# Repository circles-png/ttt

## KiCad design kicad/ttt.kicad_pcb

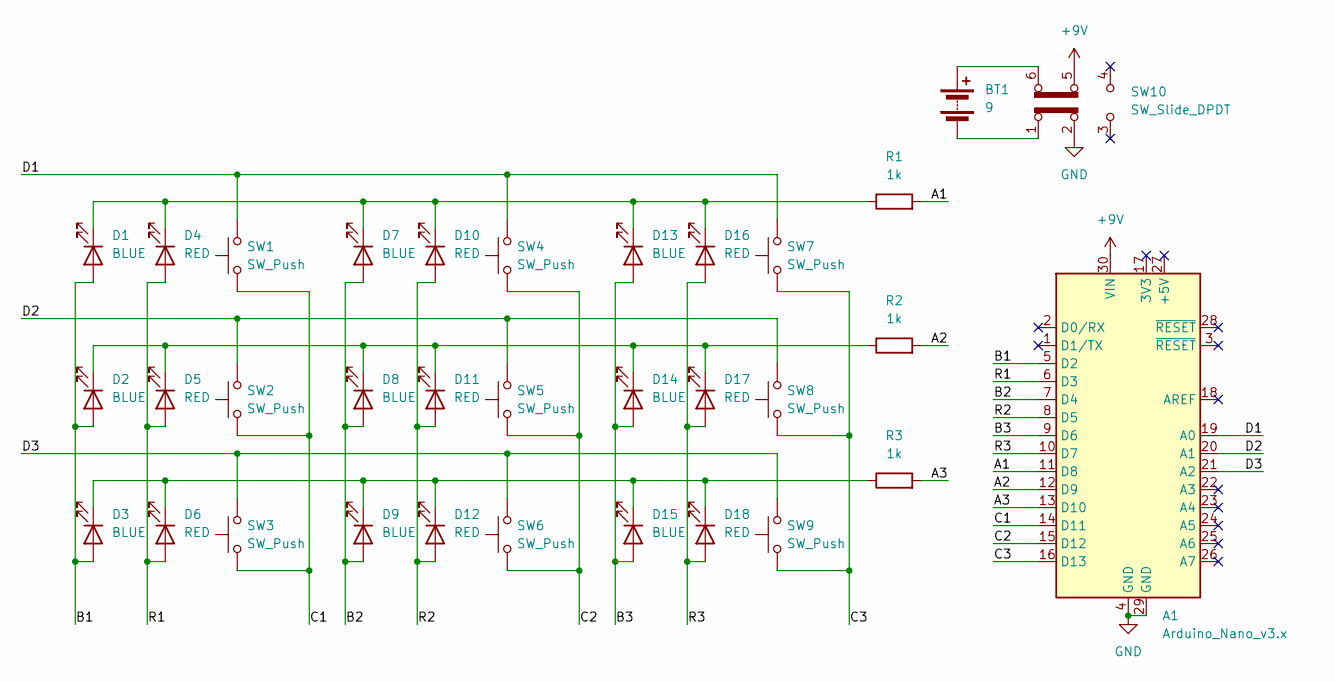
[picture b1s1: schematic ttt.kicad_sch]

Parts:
A1: Arduino_Nano_v3.x; Arduino_Nano
BT1: 9; TerminalBlock_bornier-2_P5.08mm
D1, D2, D3, D7, D8, D9, D13, D14, D15: BLUE; LED_D5.0mm
D4, D5, D6, D10, D11, D12, D16, D17, D18: RED; LED_D5.0mm
R1, R2, R3: 1k; R_Axial_DIN0207_L6.3mm_D2.5mm_P10.16mm_Horizontal
SW1, SW2, SW3, SW4, SW5, SW6, SW7, SW8, SW9: SW_Push; SW_PUSH_6mm
SW10: SW_Slide_DPDT; SW_CK_JS202011CQN_DPDT_Straight

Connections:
+9V: A1.30 (VIN), SW10.5 (B)
/A1: A1.11 (D8), R1.2
/A2: A1.12 (D9), R2.2
/A3: A1.13 (D10), R3.2
/B1: A1.5 (D2), D1.2 (A), D2.2 (A), D3.2 (A)
/B2: A1.7 (D4), D7.2 (A), D8.2 (A), D9.2 (A)
/B3: A1.9 (D6), D13.2 (A), D14.2 (A), D15.2 (A)
/C1: A1.14 (D11), SW1.1, SW2.1, SW3.1
/C2: A1.15 (D12), SW4.1, SW5.1, SW6.1
/C3: A1.16 (D13), SW7.1, SW8.1, SW9.1
/D1: A1.19 (A0), SW1.2, SW4.2, SW7.2
/D2: A1.20 (A1), SW2.2, SW5.2, SW8.2
/D3: A1.21 (A2), SW3.2, SW6.2, SW9.2
/R1: A1.6 (D3), D4.2 (A), D5.2 (A), D6.2 (A)
/R2: A1.8 (D5), D10.2 (A), D11.2 (A), D12.2 (A)
/R3: A1.10 (D7), D16.2 (A), D17.2 (A), D18.2 (A)
GND: A1.4 (GND), A1.29 (GND), SW10.2 (B)
unnamed: BT1.1 (+), SW10.6 (C)
unnamed: BT1.2 (-), SW10.1 (A)
unnamed: D1.1 (K), D4.1 (K), D7.1 (K), D10.1 (K), D13.1 (K), D16.1 (K), R1.1
unnamed: D2.1 (K), D5.1 (K), D8.1 (K), D11.1 (K), D14.1 (K), D17.1 (K), R2.1
unnamed: D3.1 (K), D6.1 (K), D9.1 (K), D12.1 (K), D15.1 (K), D18.1 (K), R3.1

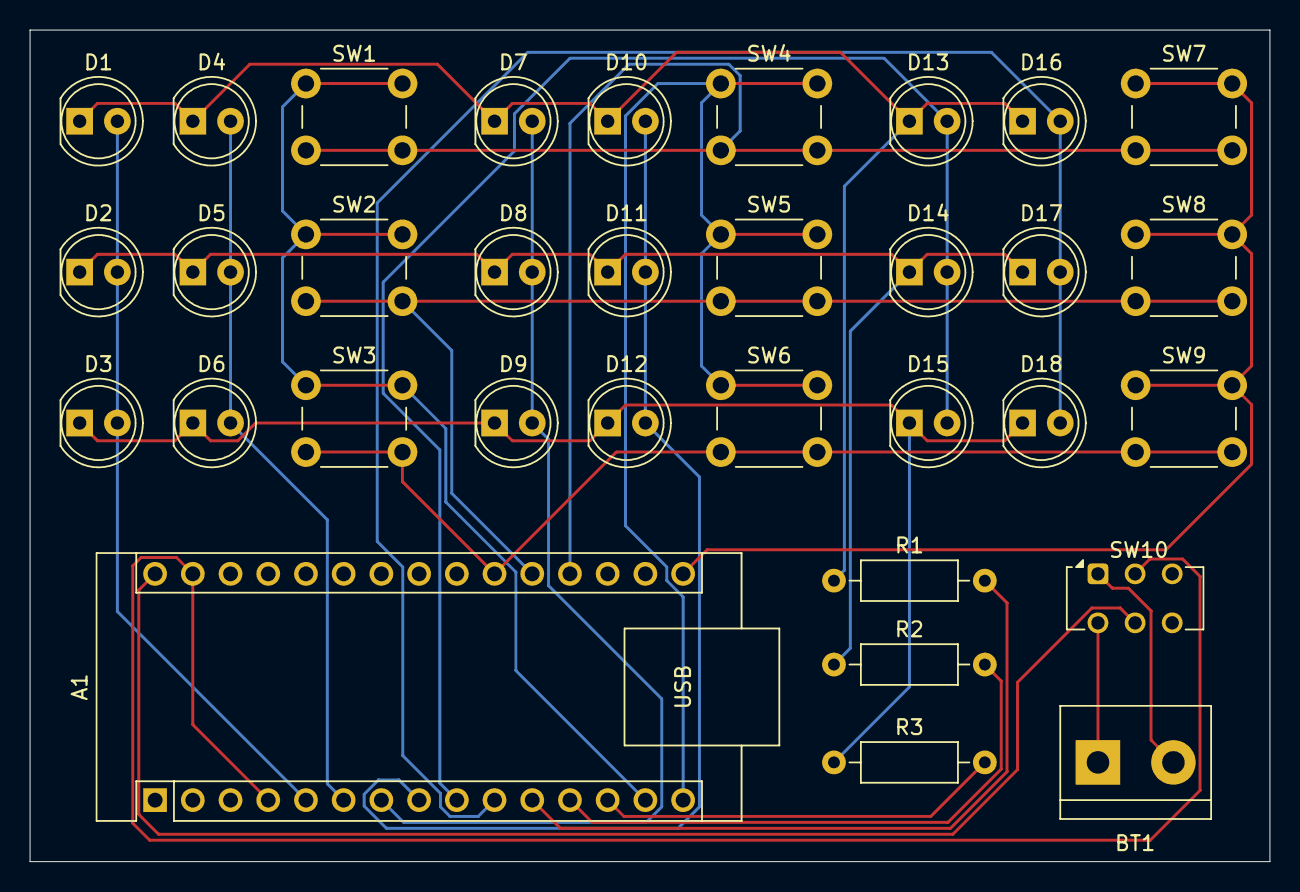
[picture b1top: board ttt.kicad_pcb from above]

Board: 2 copper layers, 83.5 x 56.0 mm, 33 parts (0 on the bottom side), 22 nets.

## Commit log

2024-11-18 Refactor game initialization and remove unused random functionality; add animation data
2024-11-24 Update configuration and build scripts for AVR target; modify KiCad schematic and main.rs button configuration
2024-11-24 Refactor random number generation and ADC initialization in main.rs
2024-11-25 Update project structure and add hexapawn game
2024-11-25 Replace unwrap() with unwrap_infallible() in button and display state handling
